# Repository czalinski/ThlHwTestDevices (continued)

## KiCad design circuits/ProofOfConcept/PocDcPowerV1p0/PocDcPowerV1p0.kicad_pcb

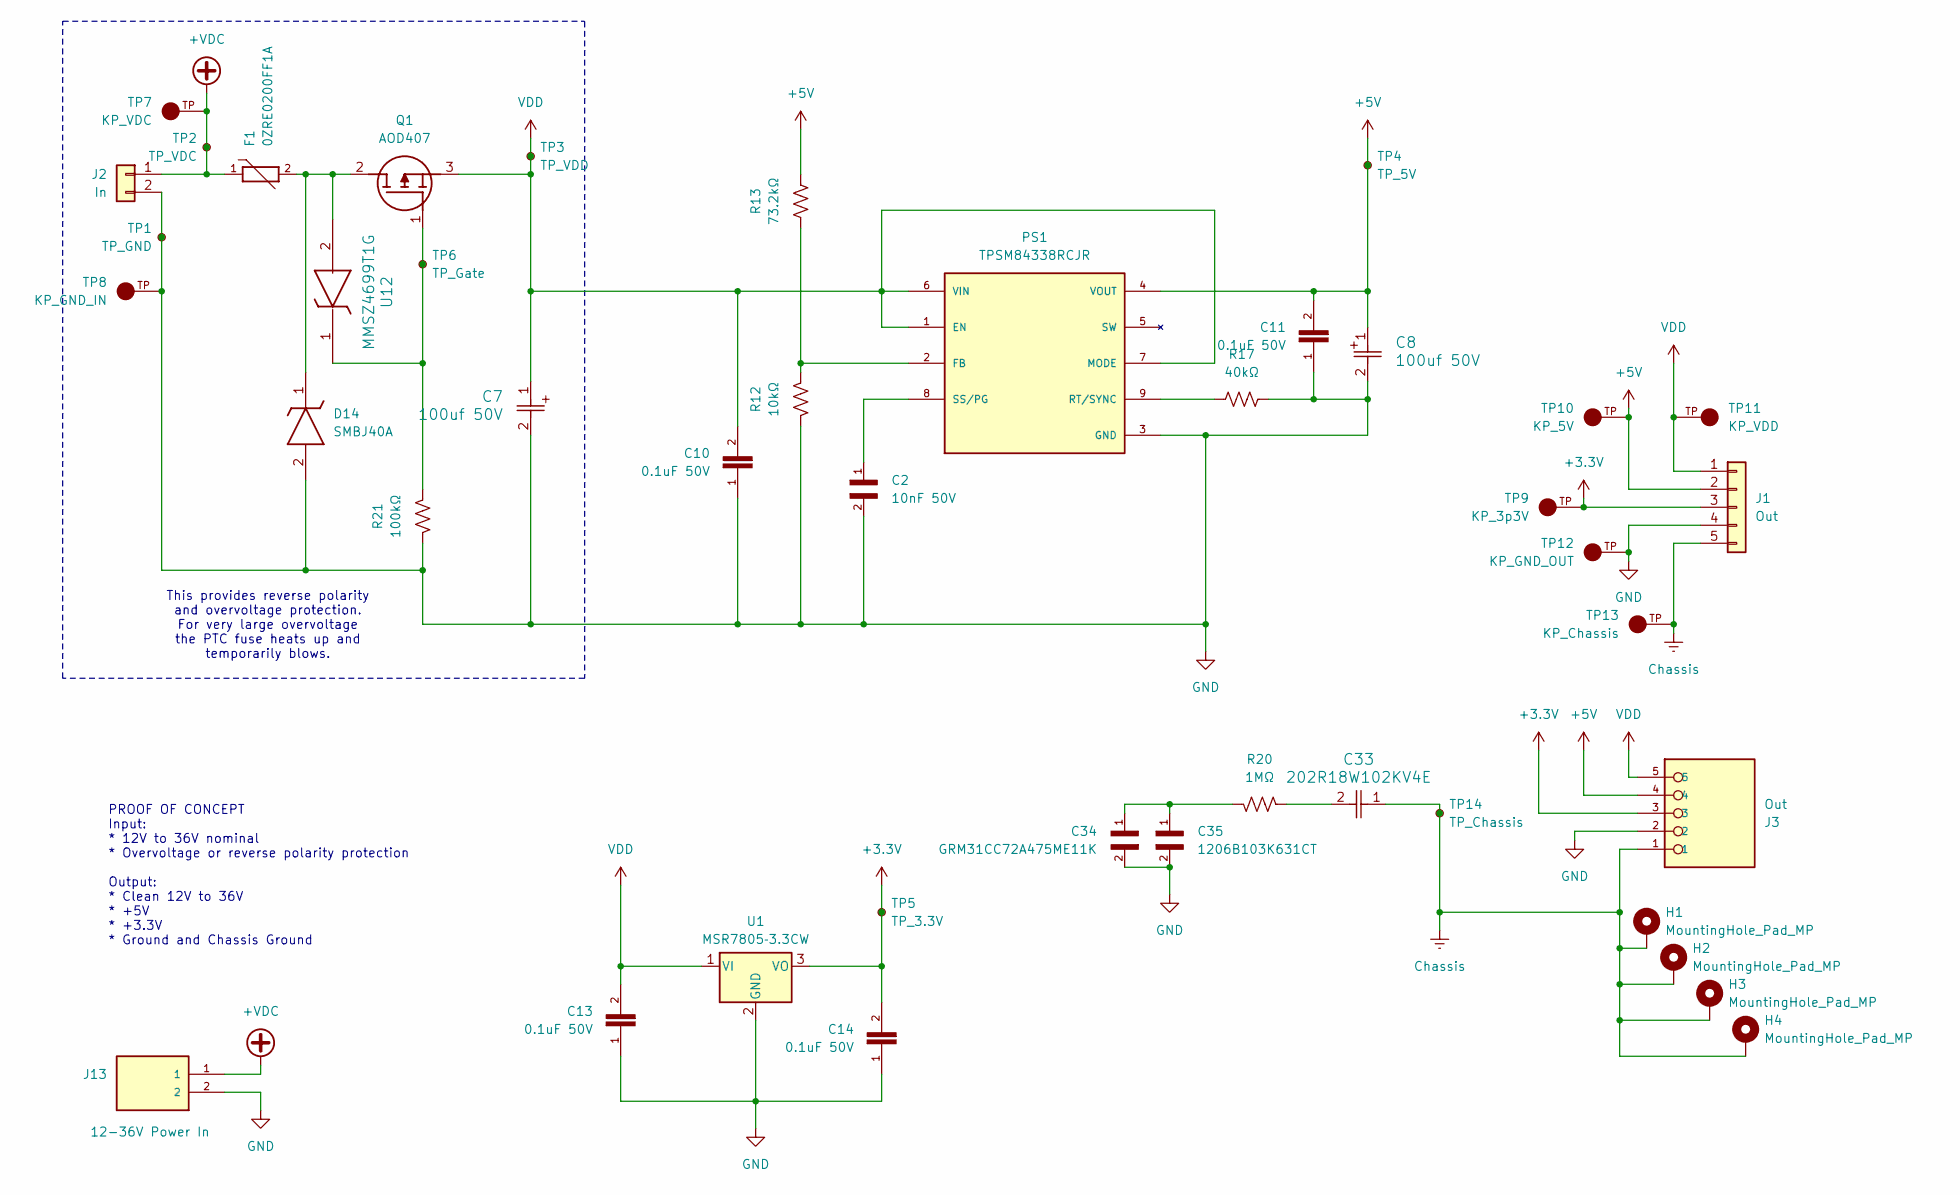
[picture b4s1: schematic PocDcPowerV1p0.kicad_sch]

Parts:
C2: 10nF 50V; CAPC3216X90N; PARTREV Jul. 2024
C7, C8: 100uf 50V; CAP_YX_8X11P5_RUB
C10, C11, C13, C14: 0.1uF 50V; CAPC2012X70
C33: 202R18W102KV4E; R18
C34: GRM31CC72A475ME11K; CAPC3216X90N; PARTREV Jul. 2024
C35: 1206B103K631CT; CAPC3216X90N; PARTREV Jul. 2024
D14: SMBJ40A; DIOM5436X265N; Manufacturer_Part_Number SMBJ40A
F1: 0ZRE0200FF1A; FUSRR1020W81L2490T610H3380; PARTREV Apr2023
H1, H2, H3, H4: MountingHole_Pad_MP; MountingHole_3.2mm_M3_Pad_Via
J1: Out; PinHeader_1x05_P2.54mm_Vertical
J2: In; PinHeader_1x02_P2.54mm_Vertical
J3: Out; PHOENIX_1990038
J13: 12-36V Power In; CUI_TB005-762-02BE
PS1: TPSM84338RCJR; CONV_TPSM84338RCJR; PARTREV November 2024
Q1: AOD407; Manufacturer_Part_Number AOD407
R12: 10kΩ; RES_1206
R13: 73.2kΩ; RES_1206
R17: 40kΩ; RES_1206
R20: 1MΩ; RES_1206
R21: 100kΩ; RES_1206
TP1: TP_GND; TestPoint_Pad_D1.0mm
TP2: TP_VDC; TestPoint_Pad_D1.0mm
TP3: TP_VDD; TestPoint_Pad_D1.0mm
TP4: TP_5V; TestPoint_Pad_D1.0mm
TP5: TP_3.3V; TestPoint_Pad_D1.0mm
TP6: TP_Gate; TestPoint_Pad_D1.0mm
TP7: KP_VDC; KEYSTONE_4954_Slot; PARTREV B; DigiKey_Part_Number 36-4954-ND
TP8: KP_GND_IN; KEYSTONE_4954_Slot; PARTREV B; DigiKey_Part_Number 36-4954-ND
TP9: KP_3p3V; KEYSTONE_4954_Slot; PARTREV B; DigiKey_Part_Number 36-4954-ND
TP10: KP_5V; KEYSTONE_4954_Slot; PARTREV B; DigiKey_Part_Number 36-4954-ND
TP11: KP_VDD; KEYSTONE_4954_Slot; PARTREV B; DigiKey_Part_Number 36-4954-ND
TP12: KP_GND_OUT; KEYSTONE_4954_Slot; PARTREV B; DigiKey_Part_Number 36-4954-ND
TP13: KP_Chassis; KEYSTONE_4954_Slot; PARTREV B; DigiKey_Part_Number 36-4954-ND
TP14: TP_Chassis; TestPoint_Pad_D1.0mm
U1: MSR7805‑3.3CW; 3-SIP
U12: MMSZ4699T1G; SOD-123_ONS

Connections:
+3.3V: C14.2, J1.3, J3.3, TP5.1 (1_1), TP9.TP, U1.3 (VO)
+5V: C8.1, C11.2, J1.2, J3.4, PS1.4 (VOUT), R13.2, TP4.1 (1_1), TP10.TP
+VDC: F1.1, J2.1, J13.1, TP2.1 (1_1), TP7.TP
Chassis: C33.1, H1.1 (MP_1), H2.1 (MP_1), H3.1 (MP_1), H4.1 (MP_1), J1.5, J3.1, TP13.TP, TP14.1 (1_1)
GND: C2.2, C7.2, C8.2, C10.1, C11.1, C13.1, C14.1, C34.2, C35.2, D14.2 (A), J1.4, J2.2, J3.2, J13.2, PS1.3 (GND), R12.2, R17.2, R21.2, TP1.1 (1_1), TP8.TP, TP12.TP, U1.2 (GND)
unnamed: C33.2, R20.1
unnamed: C34.1, C35.1, R20.2
unnamed: D14.1 (K), F1.2, Q1.2 (D), U12.2
unnamed: PS1.2 (FB), R12.1, R13.1
unnamed: PS1.9 (RT/SYNC), R17.1
unnamed: C2.1, PS1.8 (SS/PG)
unnamed: Q1.1 (G), R21.1, TP6.1 (1_1), U12.1
VDD: C7.1, C10.2, C13.2, J1.1, J3.5, PS1.1 (EN), PS1.6 (VIN), PS1.7 (MODE), Q1.3 (S), TP3.1 (1_1), TP11.TP, U1.1 (VI)

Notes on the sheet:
PROOF OF CONCEPT Input: * 12V to 36V nominal * Overvoltage or reverse polarity protection Output: * Clean 12V to 36V * +5V * +3.3V * Ground and Chassis Ground
This provides reverse polarity and overvoltage protection. For very large overvoltage the PTC fuse heats up and temporarily blows.

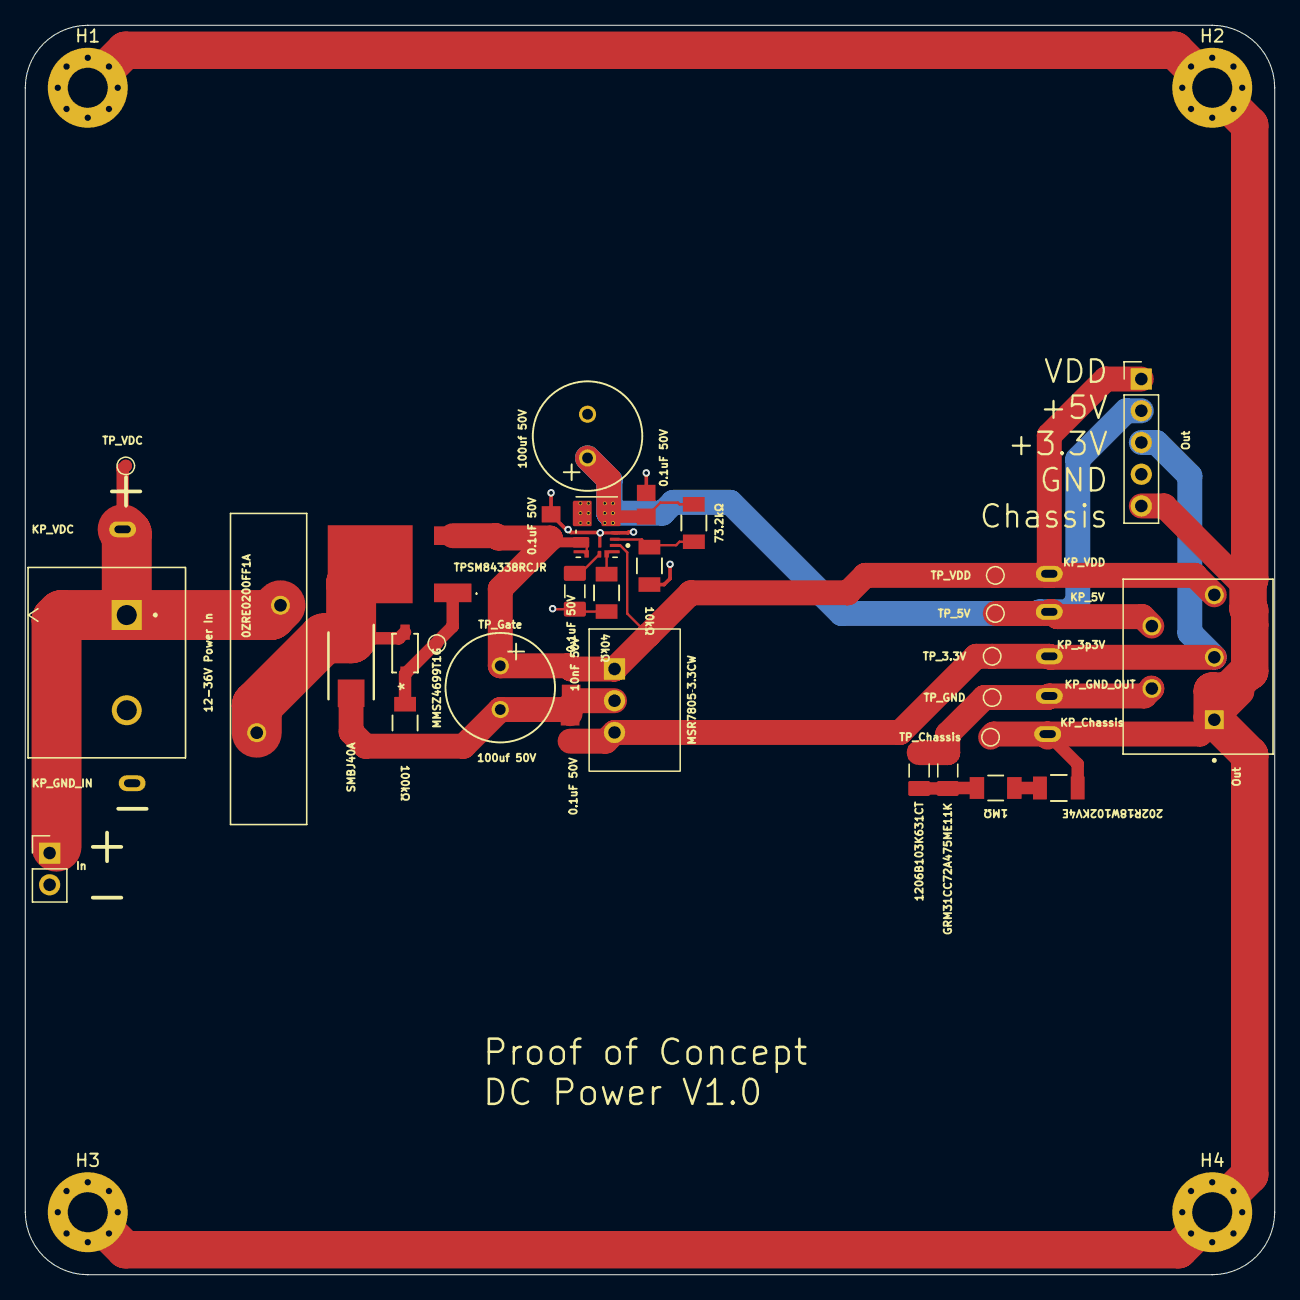
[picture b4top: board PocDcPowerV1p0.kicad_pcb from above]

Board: 2 copper layers, 100.0 x 100.0 mm, 43 parts (0 on the bottom side), 13 nets.

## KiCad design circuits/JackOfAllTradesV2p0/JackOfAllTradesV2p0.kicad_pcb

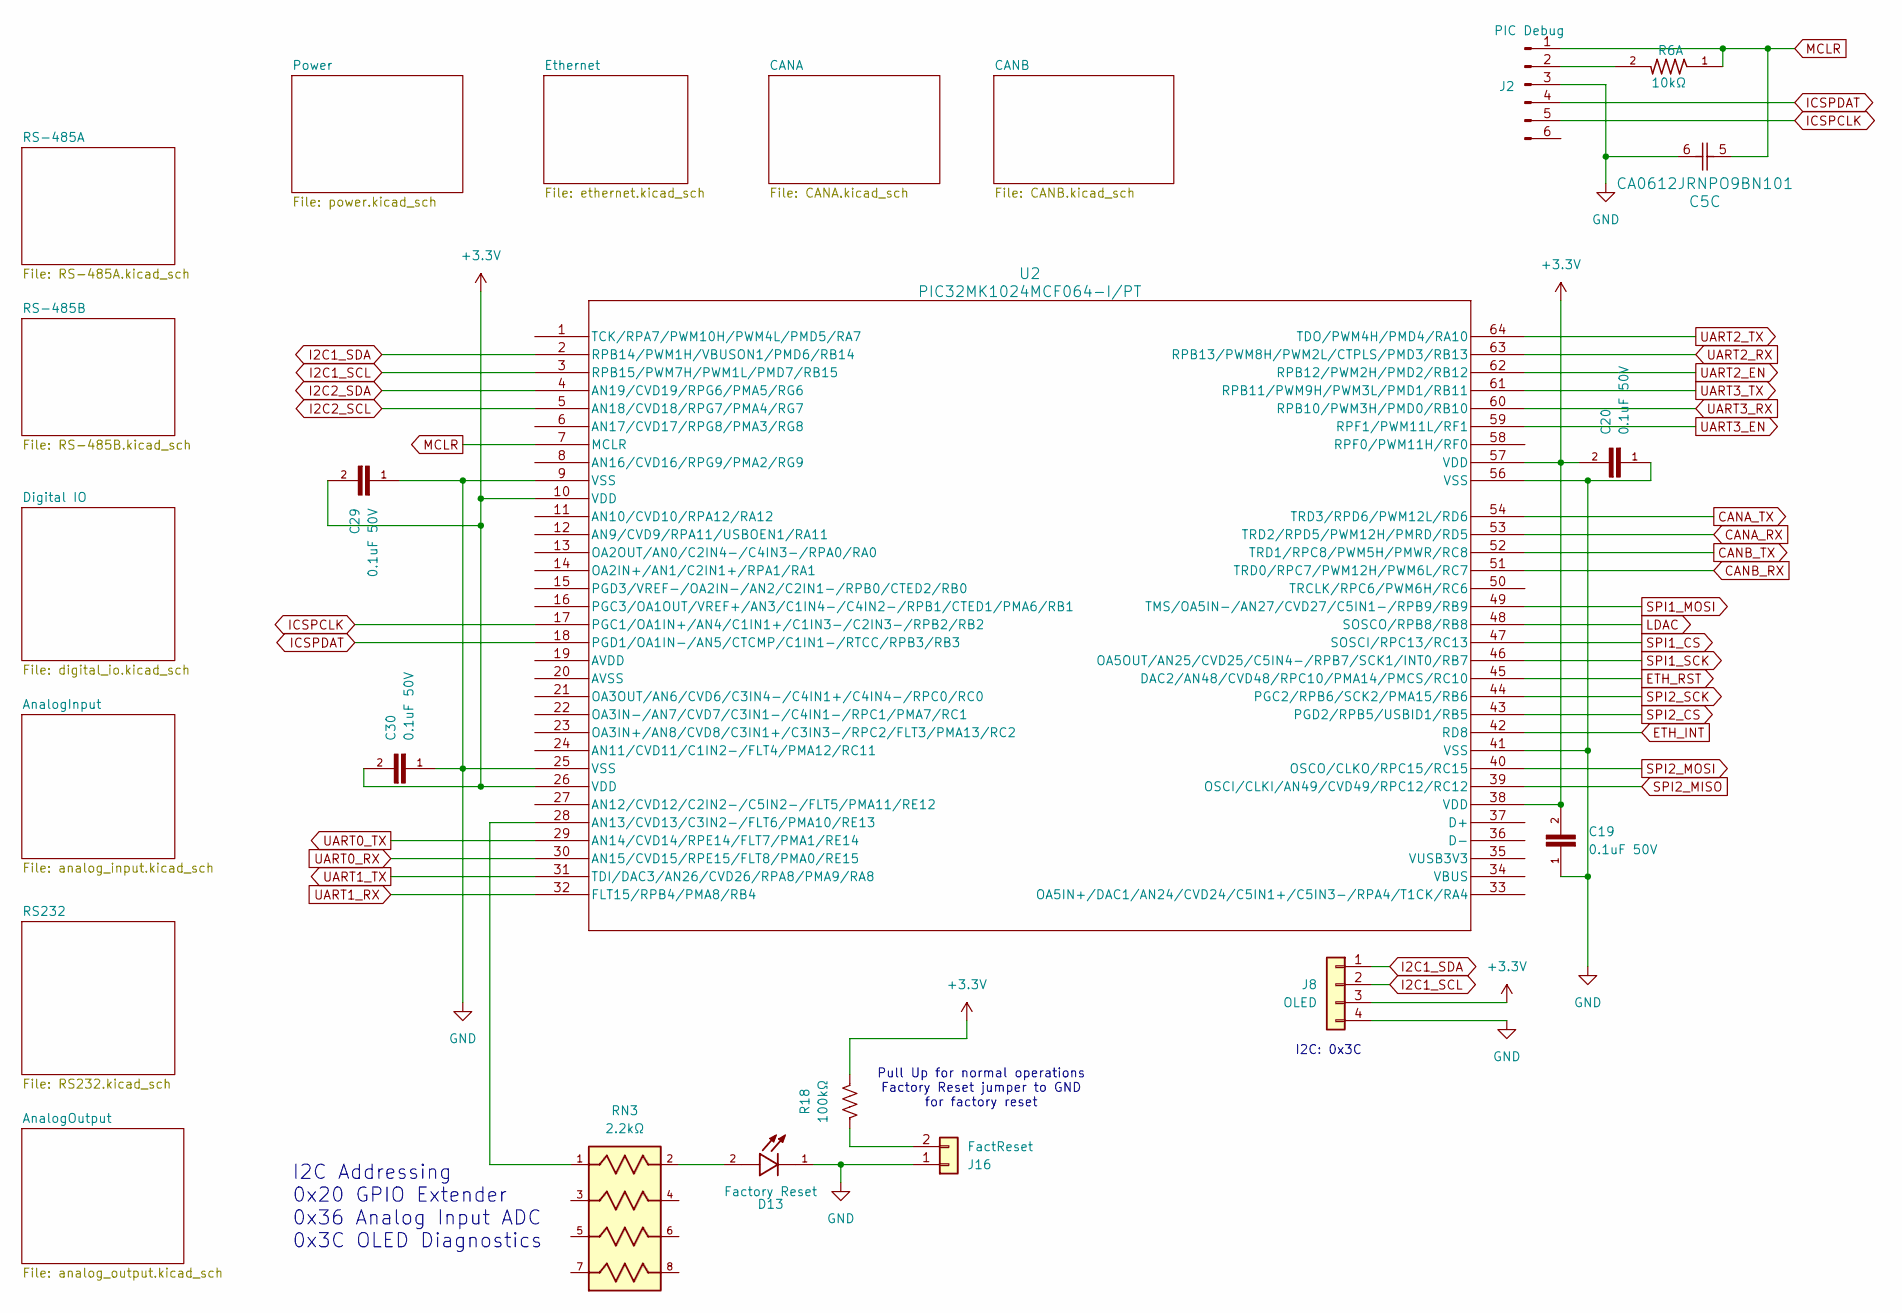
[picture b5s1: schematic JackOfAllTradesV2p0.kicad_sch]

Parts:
C5: CA0612JRNPO9BN101; CAP_CA0612_3P2X1P6_YAG
C19, C20, C29, C30: 0.1uF 50V; CAPC2012X70
D13: Factory Reset; LED_LTST-C170GKT; PARTREV I
J2: PIC Debug; PinHeader_1x06_P2.54mm_Horizontal
J8: OLED; PinHeader_1x04_P2.54mm_Vertical
J16: FactReset; PinHeader_1x02_P2.54mm_Horizontal
R6: 10kΩ; RESCAV80P320X160X70-8N
R18: 100kΩ; RES_1206
RN3: 2.2kΩ; RESCAXS50P200X100X55-8N
U2: PIC32MK1024MCF064-I/PT; TQFP64_PT_MCH

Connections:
+3.3V: C19.2, C20.2, C29.2, C30.2, J8.3, R18.1, U2.10 (VDD), U2.26 (VDD), U2.38 (VDD), U2.57 (VDD); also elsewhere on the board
CANA_RX: U2.53 (TRD2/RPD5/PWM12H/PMRD/RD5); also elsewhere on the board
CANA_TX: U2.54 (TRD3/RPD6/PWM12L/RD6); also elsewhere on the board
CANB_RX: U2.51 (TRD0/RPC7/PWM12H/PWM6L/RC7); also elsewhere on the board
CANB_TX: U2.52 (TRD1/RPC8/PWM5H/PMWR/RC8); also elsewhere on the board
ETH_INT: U2.42 (RD8); also elsewhere on the board
ETH_RST: U2.45 (DAC2/AN48/CVD48/RPC10/PMA14/PMCS/RC10); also elsewhere on the board
GND: C5.6, C19.1, C20.1, C29.1, C30.1, D13.1, J2.3, J8.4, J16.1, U2.9 (VSS), U2.25 (VSS), U2.41 (VSS), U2.56 (VSS); also elsewhere on the board
I2C1_SCL: J8.2, U2.3 (RPB15/PWM7H/PWM1L/PMD7/RB15); also elsewhere on the board
I2C1_SDA: J8.1, U2.2 (RPB14/PWM1H/VBUSON1/PMD6/RB14); also elsewhere on the board
I2C2_SCL: U2.5 (AN18/CVD18/RPG7/PMA4/RG7)
I2C2_SDA: U2.4 (AN19/CVD19/RPG6/PMA5/RG6)
ICSPCLK: J2.5, U2.17 (PGC1/OA1IN+/AN4/C1IN1+/C1IN3-/C2IN3-/RP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)
ICSPDAT: J2.4, U2.18 (PGD1/OA1IN-/AN5/CTCMP/C1IN1-/RTCC/RPB3/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)
LDAC: U2.48 (SOSCO/RPB8/RB8); also elsewhere on the board
MCLR: C5.5, J2.1, R6.1, U2.7 (MCLR)
unnamed: D13.2, RN3.2
unnamed: J2.2, R6.2
unnamed: J16.2, R18.2
unnamed: RN3.1, U2.28 (AN13/CVD13/C3IN2-/FLT6/PMA10/RE13)
SPI1_CS: U2.47 (SOSCI/RPC13/RC13); also elsewhere on the board
SPI1_MOSI: U2.49 (TMS/OA5IN-/AN27/CVD27/C5IN1-/RPB9/RB9); also elsewhere on the board
SPI1_SCK: U2.46 (OA5OUT/AN25/CVD25/C5IN4-/RPB7/SCK1/INT0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); also elsewhere on the board
SPI2_CS: U2.43 (PGD2/RPB5/USBID1/RB5); also elsewhere on the board
SPI2_MISO: U2.39 (OSCI/CLKI/AN49/CVD49/RPC12/RC12); also elsewhere on the board
SPI2_MOSI: U2.40 (OSCO/CLKO/RPC15/RC15); also elsewhere on the board
SPI2_SCK: U2.44 (PGC2/RPB6/SCK2/PMA15/RB6); also elsewhere on the board
UART0_RX: U2.30 (AN15/CVD15/RPE15/FLT8/PMA0/RE15); also elsewhere on the board
UART0_TX: U2.29 (AN14/CVD14/RPE14/FLT7/PMA1/RE14); also elsewhere on the board
UART1_RX: U2.32 (FLT15/RPB4/PMA8/RB4); also elsewhere on the board
UART1_TX: U2.31 (TDI/DAC3/AN26/CVD26/RPA8/PMA9/RA8); also elsewhere on the board
UART2_RX: U2.63 (RPB13/PWM8H/PWM2L/CTPLS/PMD3/RB13); also elsewhere on the board
UART2_TX: U2.64 (TDO/PWM4H/PMD4/RA10); also elsewhere on the board

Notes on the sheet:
Pull Up for normal operations Factory Reset jumper to GND for factory reset
I2C: 0x3C
I2C Addressing 0x20 GPIO Extender 0x36 Analog Input ADC 0x3C OLED Diagnostics

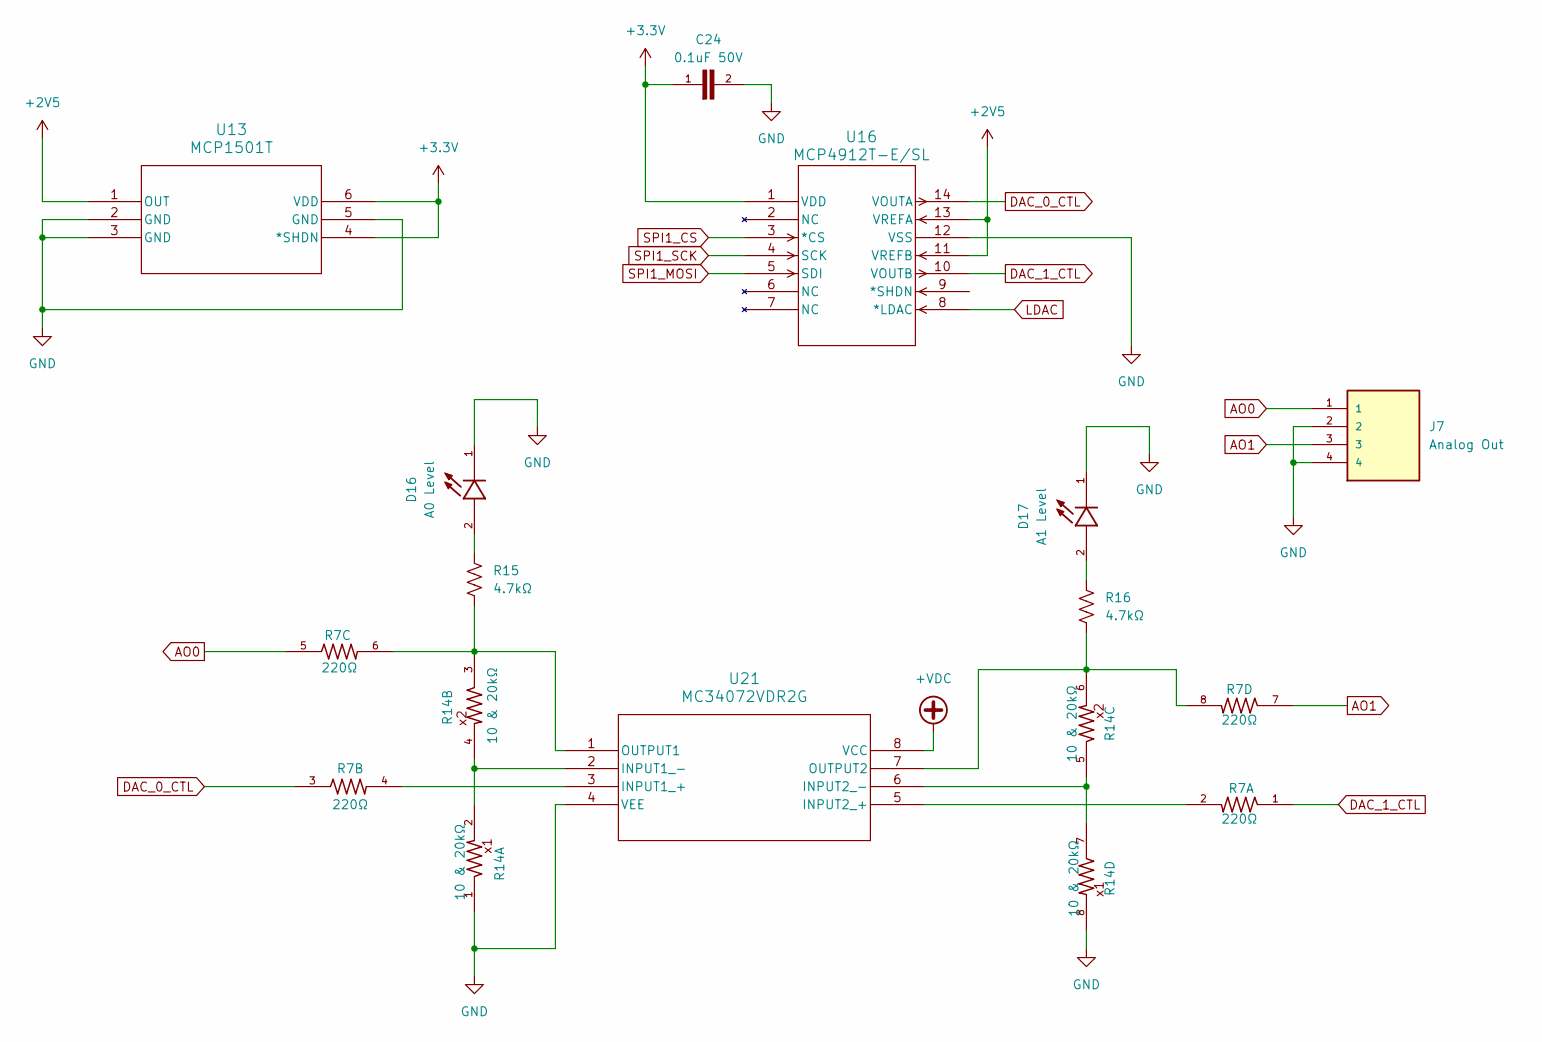
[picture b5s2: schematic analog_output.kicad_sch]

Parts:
C24: 0.1uF 50V; CAPC2012X70
D16: A0 Level; LED_LTST-C170GKT; PARTREV I
D17: A1 Level; LED_LTST-C170GKT; PARTREV I
J7: Analog Out; TE_1985218; PARTREV 29.03.2021
R7: 220Ω; RESCAV80P320X160X70-8N
R14: 10 & 20kΩ; RESCAV80P320X160X70-8N
R15, R16: 4.7kΩ; RES_1206
U13: MCP1501T; SOT-23_OT&slash_OTY_MCH
U16: MCP4912T-E/SL; SOIC14-N_MC_MCH
U21: MC34072VDR2G; SOIC8_ONS

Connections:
+2V5: U13.1 (OUT), U16.11 (VREFB), U16.13 (VREFA)
+3.3V: C24.1, U13.4 (*SHDN), U13.6 (VDD), U16.1 (VDD); also elsewhere on the board
+VDC: U21.8 (VCC); also elsewhere on the board
AO0: J7.1, R7.5
AO1: J7.3, R7.7
DAC_0_CTL: R7.3, U16.14 (VOUTA)
DAC_1_CTL: R7.1, U16.10 (VOUTB)
GND: C24.2, D16.1, D17.1, J7.2, J7.4, R14.1, R14.8, U13.2 (GND), U13.3 (GND), U13.5 (GND), U16.12 (VSS), U21.4 (VEE); also elsewhere on the board
LDAC: U16.8 (*LDAC); also elsewhere on the board
unnamed: D16.2, R15.1
unnamed: D17.2, R16.1
unnamed: R7.4, U21.3 (INPUT1_+)
unnamed: R14.2, R14.4, U21.2 (INPUT1_-)
unnamed: R7.2, U21.5 (INPUT2_+)
unnamed: R14.5, R14.7, U21.6 (INPUT2_-)
unnamed: R7.6, R14.3, R15.2, U21.1 (OUTPUT1)
unnamed: R7.8, R14.6, R16.2, U21.7 (OUTPUT2)
SPI1_CS: U16.3 (*CS); also elsewhere on the board
SPI1_MOSI: U16.5 (SDI); also elsewhere on the board
SPI1_SCK: U16.4 (SCK); also elsewhere on the board

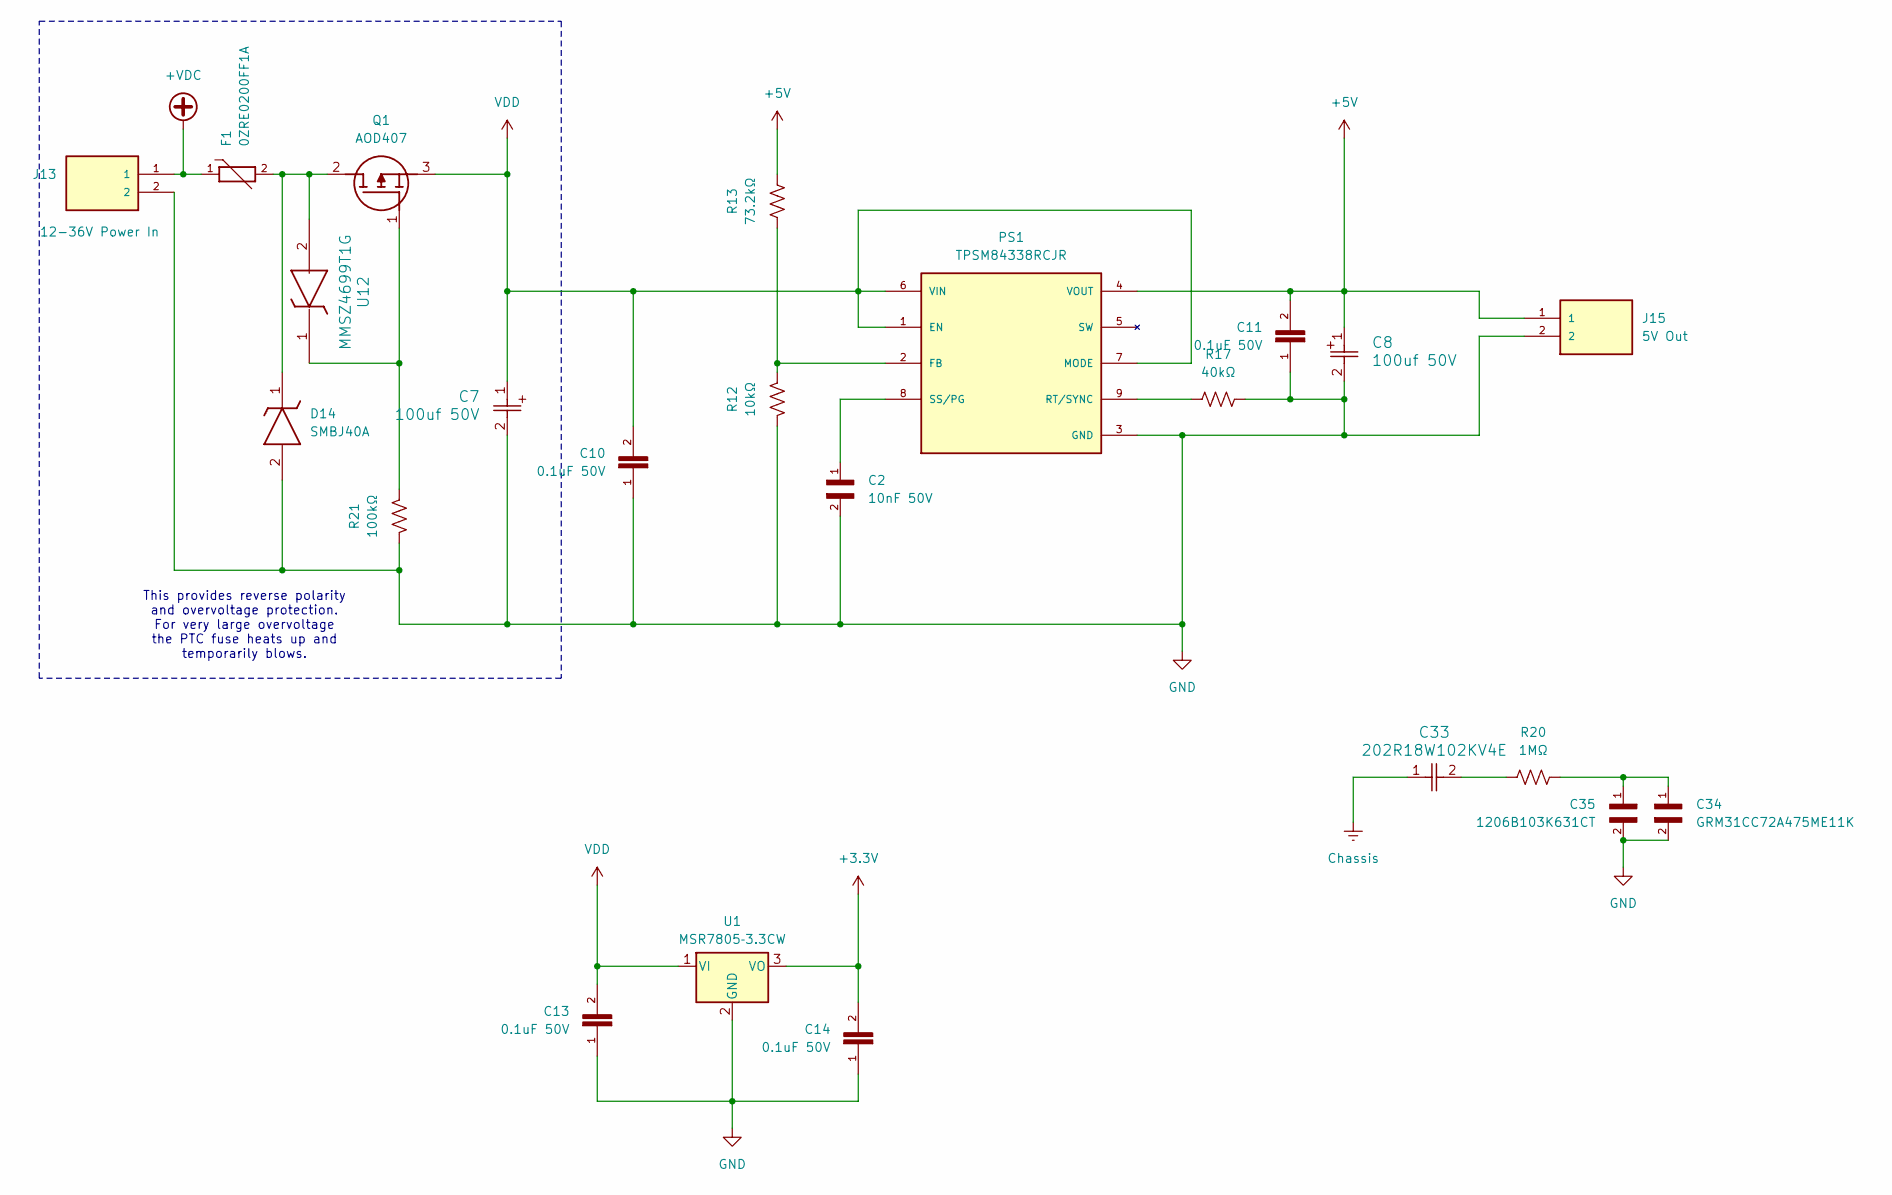
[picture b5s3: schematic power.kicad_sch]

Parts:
C2: 10nF 50V; CAPC3216X90N; PARTREV Jul. 2024
C7, C8: 100uf 50V; CAP_YX_8X11P5_RUB
C10, C11, C13, C14: 0.1uF 50V; CAPC2012X70
C33: 202R18W102KV4E; R18
C34: GRM31CC72A475ME11K; CAPC3216X90N; PARTREV Jul. 2024
C35: 1206B103K631CT; CAPC3216X90N; PARTREV Jul. 2024
D14: SMBJ40A; DIOM5436X265N; Manufacturer_Part_Number SMBJ40A
F1: 0ZRE0200FF1A; FUSRR1020W81L2490T610H3380; PARTREV Apr2023
J13: 12-36V Power In; CUI_TB005-762-02BE
J15: 5V Out; CUI_TB005-762-02BE
PS1: TPSM84338RCJR; CONV_TPSM84338RCJR; PARTREV November 2024
Q1: AOD407; Manufacturer_Part_Number AOD407
R12: 10kΩ; RES_1206
R13: 73.2kΩ; RES_1206
R17: 40kΩ; RES_1206
R20: 1MΩ; RES_1206
R21: 100kΩ; RES_1206
U1: MSR7805‑3.3CW; 3-SIP
U12: MMSZ4699T1G; SOD-123_ONS

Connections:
+3.3V: C14.2, U1.3 (VO); also elsewhere on the board
+5V: C8.1, C11.2, J15.1, PS1.4 (VOUT), R13.2; also elsewhere on the board
+VDC: F1.1, J13.1; also elsewhere on the board
Chassis: C33.1; also elsewhere on the board
GND: C2.2, C7.2, C8.2, C10.1, C11.1, C13.1, C14.1, C34.2, C35.2, D14.2 (A), J13.2, J15.2, PS1.3 (GND), R12.2, R17.2, R21.2, U1.2 (GND); also elsewhere on the board
unnamed: C33.2, R20.1
unnamed: C34.1, C35.1, R20.2
unnamed: D14.1 (K), F1.2, Q1.2 (D), U12.2
unnamed: PS1.2 (FB), R12.1, R13.1
unnamed: PS1.9 (RT/SYNC), R17.1
unnamed: C2.1, PS1.8 (SS/PG)
unnamed: Q1.1 (G), R21.1, U12.1
VDD: C7.1, C10.2, C13.2, PS1.1 (EN), PS1.6 (VIN), PS1.7 (MODE), Q1.3 (S), U1.1 (VI)

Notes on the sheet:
This provides reverse polarity and overvoltage protection. For very large overvoltage the PTC fuse heats up and temporarily blows.

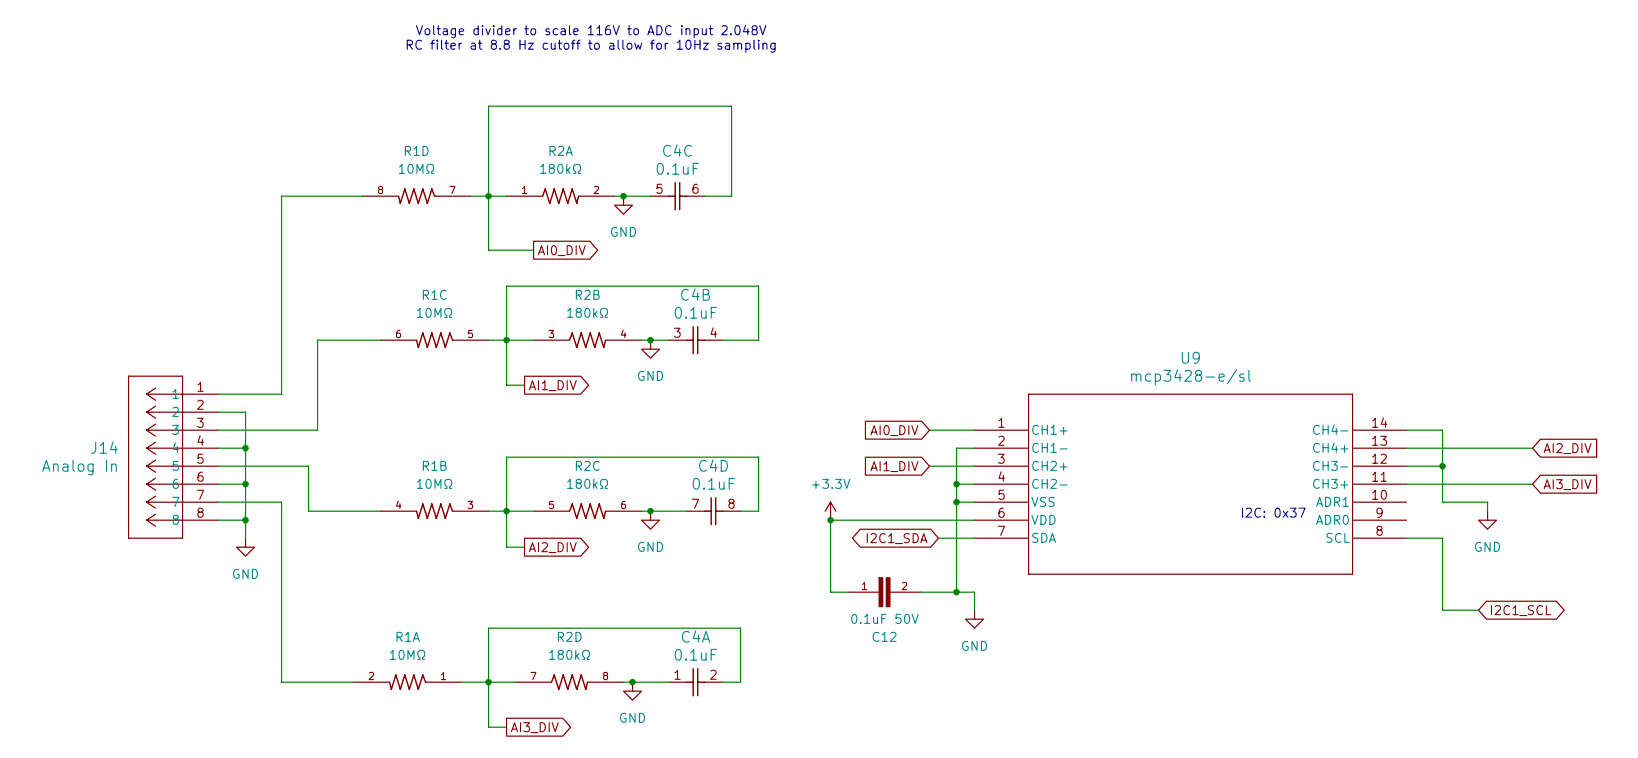
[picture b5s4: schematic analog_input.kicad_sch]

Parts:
C4: 0.1uF; CAP_CA0612_3P2X1P6_YAG
C12: 0.1uF 50V; CAPC2012X70
J14: Analog In; CONN_1989803_PXC
R1: 10MΩ; RESCAV80P320X160X70-8N
R2: 180kΩ; RESCAV80P320X160X70-8N
U9: mcp3428-e/sl; SOIC14-N_MC_MCH

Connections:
+3.3V: C12.1, U9.6 (VDD); also elsewhere on the board
AI0_DIV: C4.6, R1.7, R2.1, U9.1 (CH1+)
AI1_DIV: C4.4, R1.5, R2.3, U9.3 (CH2+)
AI2_DIV: C4.8, R1.3, R2.5, U9.13 (CH4+)
AI3_DIV: C4.2, R1.1, R2.7, U9.11 (CH3+)
GND: C4.1, C4.3, C4.5, C4.7, C12.2, J14.2, J14.4, J14.6, J14.8, R2.2, R2.4, R2.6, R2.8, U9.2 (CH1-), U9.4 (CH2-), U9.5 (VSS), U9.12 (CH3-), U9.14 (CH4-); also elsewhere on the board
I2C1_SCL: U9.8 (SCL); also elsewhere on the board
I2C1_SDA: U9.7 (SDA); also elsewhere on the board
unnamed: J14.1, R1.8
unnamed: J14.3, R1.6
unnamed: J14.5, R1.4
unnamed: J14.7, R1.2

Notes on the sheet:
Voltage divider to scale 116V to ADC input 2.048V RC filter at 8.8 Hz cutoff to allow for 10Hz sampling
I2C: 0x37

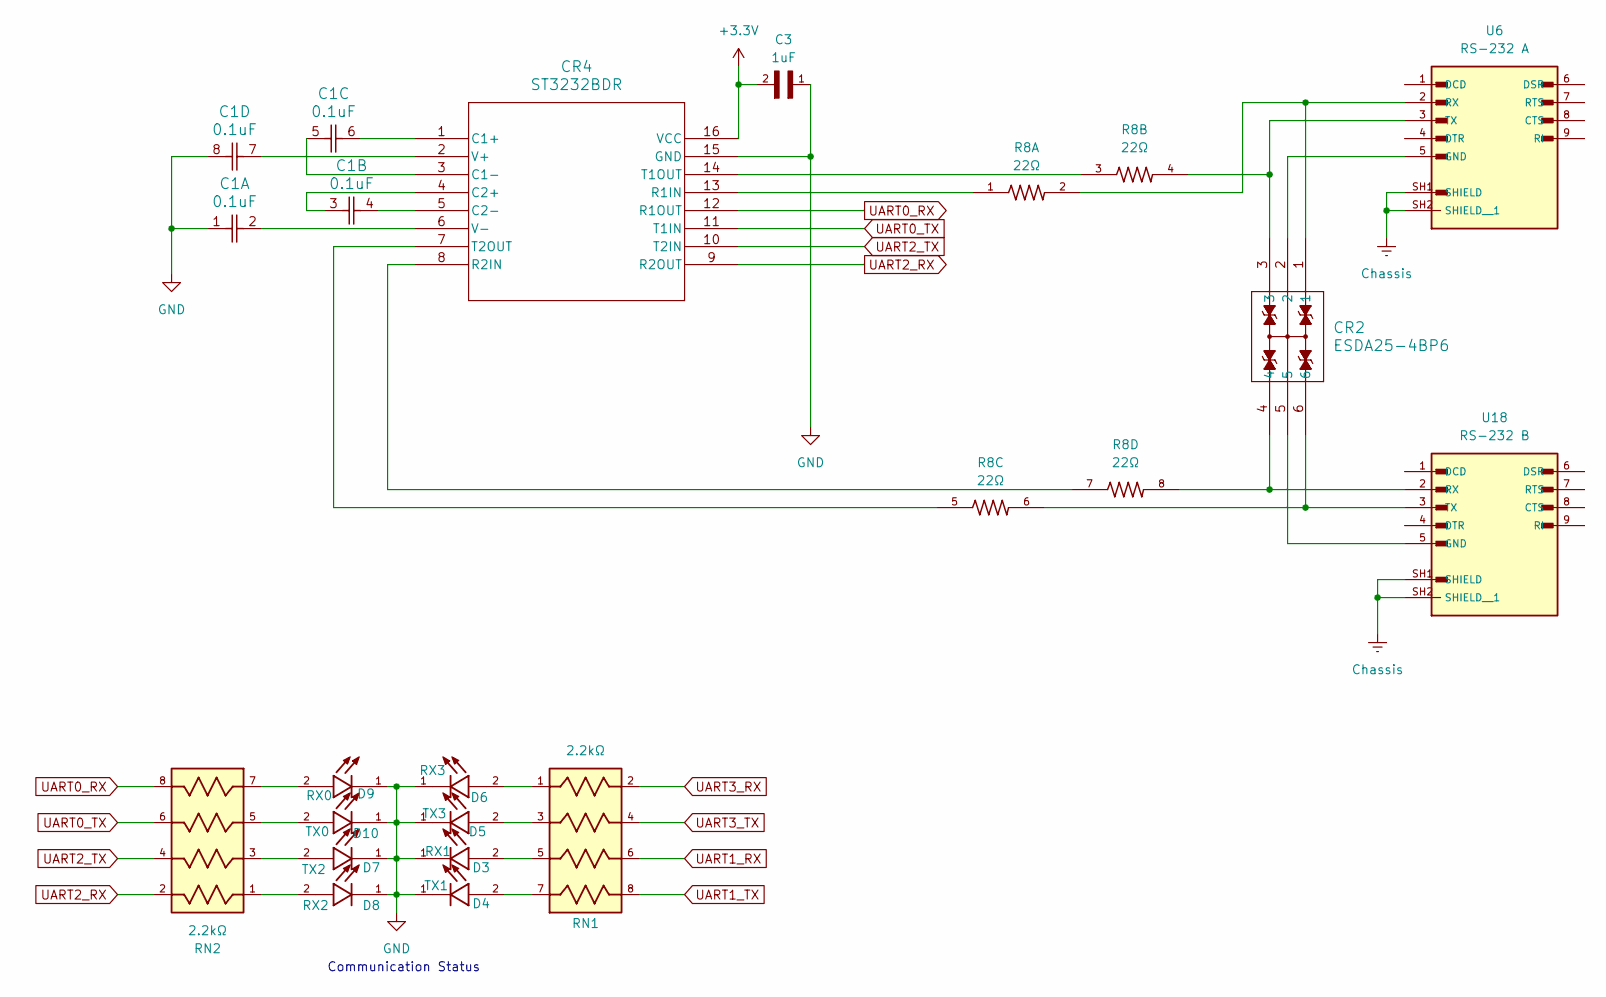
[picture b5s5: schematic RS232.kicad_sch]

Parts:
C1: 0.1uF; CAP_CA0612_3P2X1P6_YAG
C3: 1uF; CAPC1608X90N
CR2: ESDA25-4BP6; SOT666_ESDA25_STM
CR4: ST3232BDR; SO-16_STM
D3: RX1; LED_LTST-C170GKT; PARTREV I
D4: TX1; LED_LTST-C170GKT; PARTREV I
D5: TX3; LED_LTST-C170GKT; PARTREV I
D6: RX3; LED_LTST-C170GKT; PARTREV I
D7: TX2; LED_LTST-C170GKT; PARTREV I
D8: RX2; LED_LTST-C170GKT; PARTREV I
D9: RX0; LED_LTST-C170GKT; PARTREV I
D10: TX0; LED_LTST-C170GKT; PARTREV I
R8: 22Ω; RESCAV80P320X160X70-8N
RN1, RN2: 2.2kΩ; RESCAXS50P200X100X55-8N
U6: RS-232 A; ASSMANN_A-DS_09_A_KG-T2S
U18: RS-232 B; ASSMANN_A-DS_09_A_KG-T2S

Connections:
+3.3V: C3.2, CR4.16 (VCC); also elsewhere on the board
Chassis: U6.SH1 (SHIELD), U6.SH2 (SHIELD__1), U18.SH1 (SHIELD), U18.SH2 (SHIELD__1); also elsewhere on the board
GND: C1.1, C1.8, C3.1, CR4.15 (GND), D3.1, D4.1, D5.1, D6.1, D7.1, D8.1, D9.1, D10.1; also elsewhere on the board
unnamed: C1.6, CR4.1 (C1+)
unnamed: C1.5, CR4.3 (C1-)
unnamed: C1.3, CR4.4 (C2+)
unnamed: C1.4, CR4.5 (C2-)
unnamed: CR4.13 (R1IN), R8.1
unnamed: CR4.8 (R2IN), R8.7
unnamed: CR4.14 (T1OUT), R8.3
unnamed: CR4.7 (T2OUT), R8.5
unnamed: C1.7, CR4.2 (V+)
unnamed: C1.2, CR4.6 (V-)
unnamed: D3.2, RN1.5
unnamed: D4.2, RN1.7
unnamed: D5.2, RN1.3
unnamed: D6.2, RN1.1
unnamed: D7.2, RN2.3
unnamed: D8.2, RN2.1
unnamed: D9.2, RN2.7
unnamed: D10.2, RN2.5
unnamed: CR2.2, U6.5 (GND)
unnamed: CR2.1, R8.2, U6.2 (RX)
unnamed: CR2.3, R8.4, U6.3 (TX)
unnamed: CR2.5, U18.5 (GND)
unnamed: CR2.4, R8.8, U18.2 (RX)
unnamed: CR2.6, R8.6, U18.3 (TX)
UART0_RX: CR4.12 (R1OUT), RN2.8; also elsewhere on the board
UART0_TX: CR4.11 (T1IN), RN2.6; also elsewhere on the board
UART1_RX: RN1.6; also elsewhere on the board
UART1_TX: RN1.8; also elsewhere on the board
UART2_RX: CR4.9 (R2OUT), RN2.2; also elsewhere on the board
UART2_TX: CR4.10 (T2IN), RN2.4; also elsewhere on the board

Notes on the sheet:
Communication Status

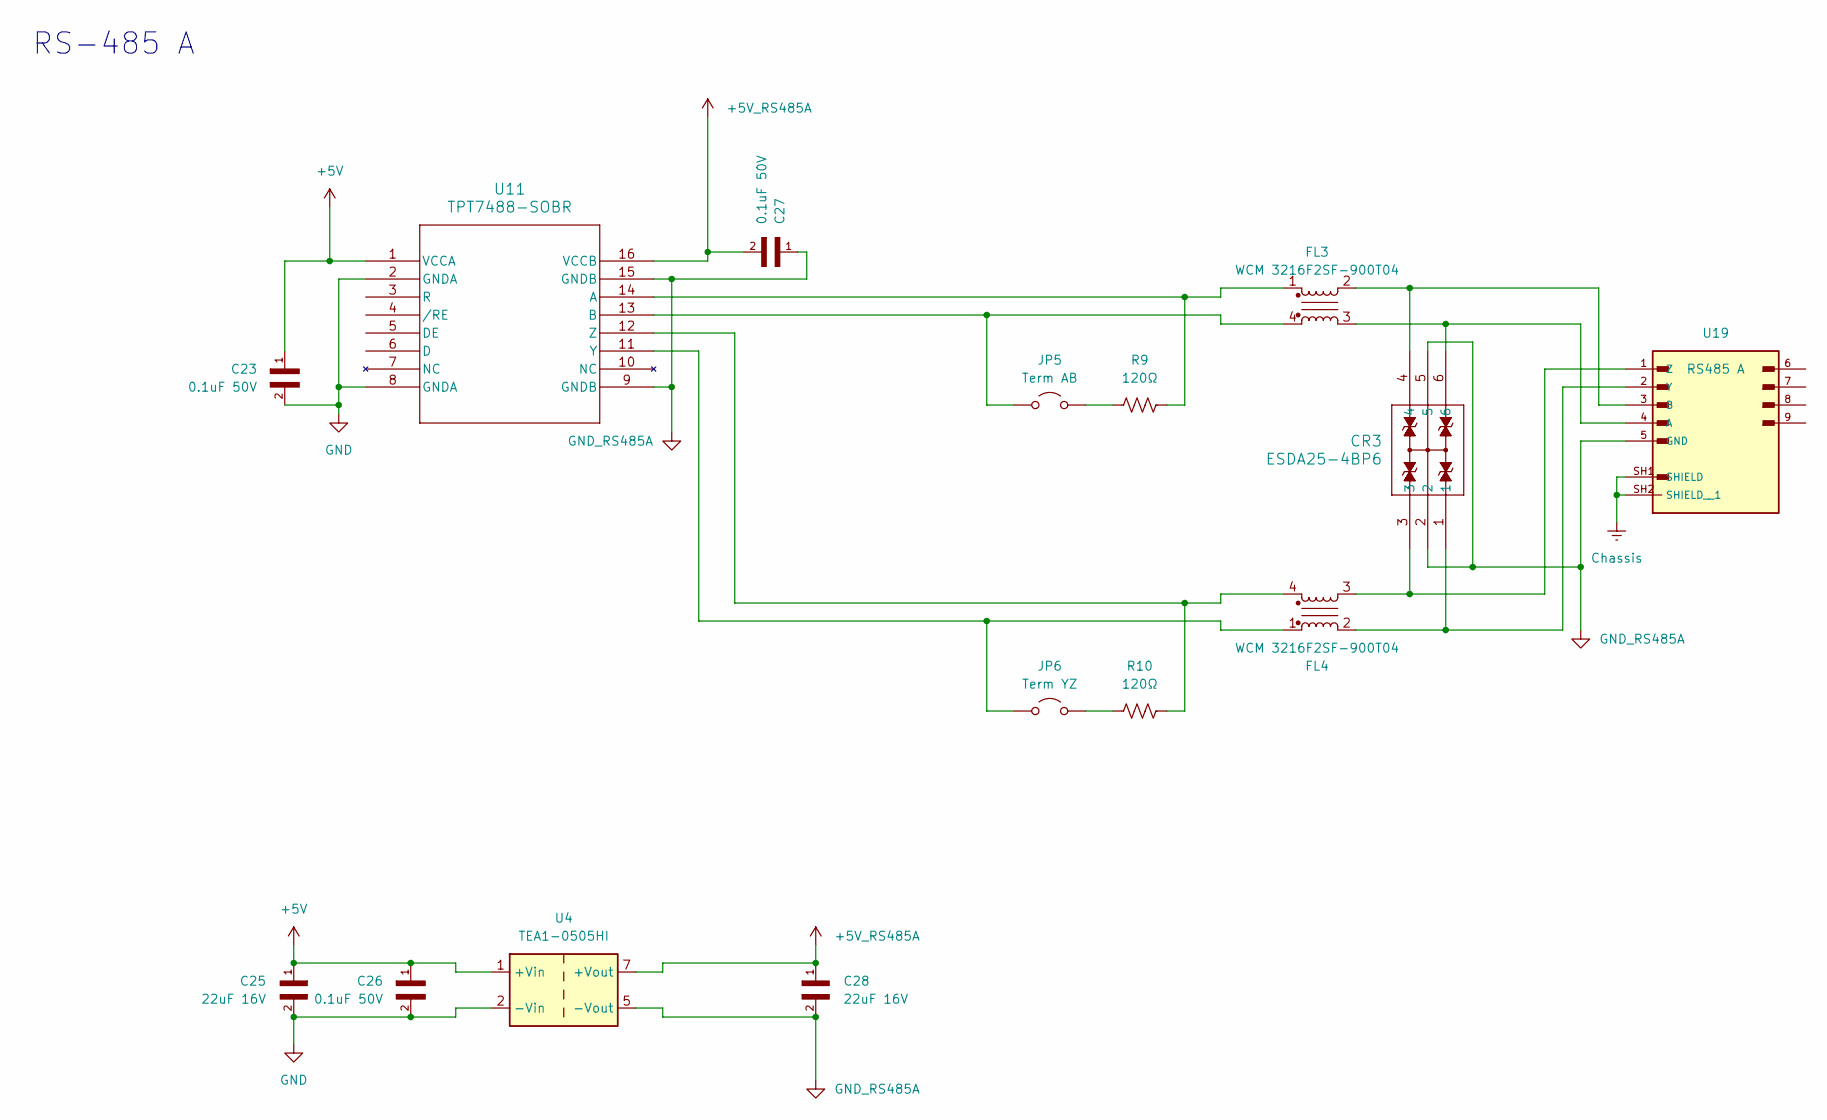
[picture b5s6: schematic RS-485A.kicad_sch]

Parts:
C23, C26, C27: 0.1uF 50V; CAPC2012X70
C25, C28: 22uF 16V; CAPC3216X95N
CR3: ESDA25-4BP6; SOT666_ESDA25_STM
FL3, FL4: WCM 3216F2SF-900T04; WCM 3216F2SF-900T04-1206
JP5: Term AB; PinHeader_1x02_P2.54mm_Vertical
JP6: Term YZ; PinHeader_1x02_P2.54mm_Vertical
R9, R10: 120Ω; RES_1206
U4: TEA1-0505HI; Converter_DCDC_TRACO_TEA1-xxxxHI_THT
U11: TPT7488-SOBR; SOBWSOP-16-A_TPK
U19: RS485 A; ASSMANN_A-DS_09_A_KG-T2S

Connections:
+5V: C23.1, C25.1, C26.1, U4.1 (+Vin), U11.1 (VCCA); also elsewhere on the board
+5V_RS485A: C27.2, C28.1, U4.7 (+Vout), U11.16 (VCCB)
Chassis: U19.SH1 (SHIELD), U19.SH2 (SHIELD__1); also elsewhere on the board
GND: C23.2, C25.2, C26.2, U4.2 (-Vin), U11.2 (GNDA), U11.8 (GNDA); also elsewhere on the board
GND_RS485A: C27.1, C28.2, CR3.2, CR3.5, U4.5 (-Vout), U11.9 (GNDB), U11.15 (GNDB), U19.5 (GND); also elsewhere on the board
unnamed: JP5.1 (A), R9.1
unnamed: FL3.4, JP5.2 (B), U11.13 (B)
unnamed: JP6.1 (A), R10.1
unnamed: FL4.1, JP6.2 (B), U11.11 (Y)
unnamed: FL3.1, R9.2, U11.14 (A)
unnamed: FL4.4, R10.2, U11.12 (Z)
unnamed: CR3.6, FL3.3, U19.4 (A)
unnamed: CR3.4, FL3.2, U19.3 (B)
unnamed: CR3.1, FL4.2, U19.2 (Y)
unnamed: CR3.3, FL4.3, U19.1 (Z)

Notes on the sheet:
RS-485 A
